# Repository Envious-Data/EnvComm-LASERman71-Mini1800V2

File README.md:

# EnvComm-LASERman71-Mini1800V2
 A custom keyboard commissioned by Laserman71

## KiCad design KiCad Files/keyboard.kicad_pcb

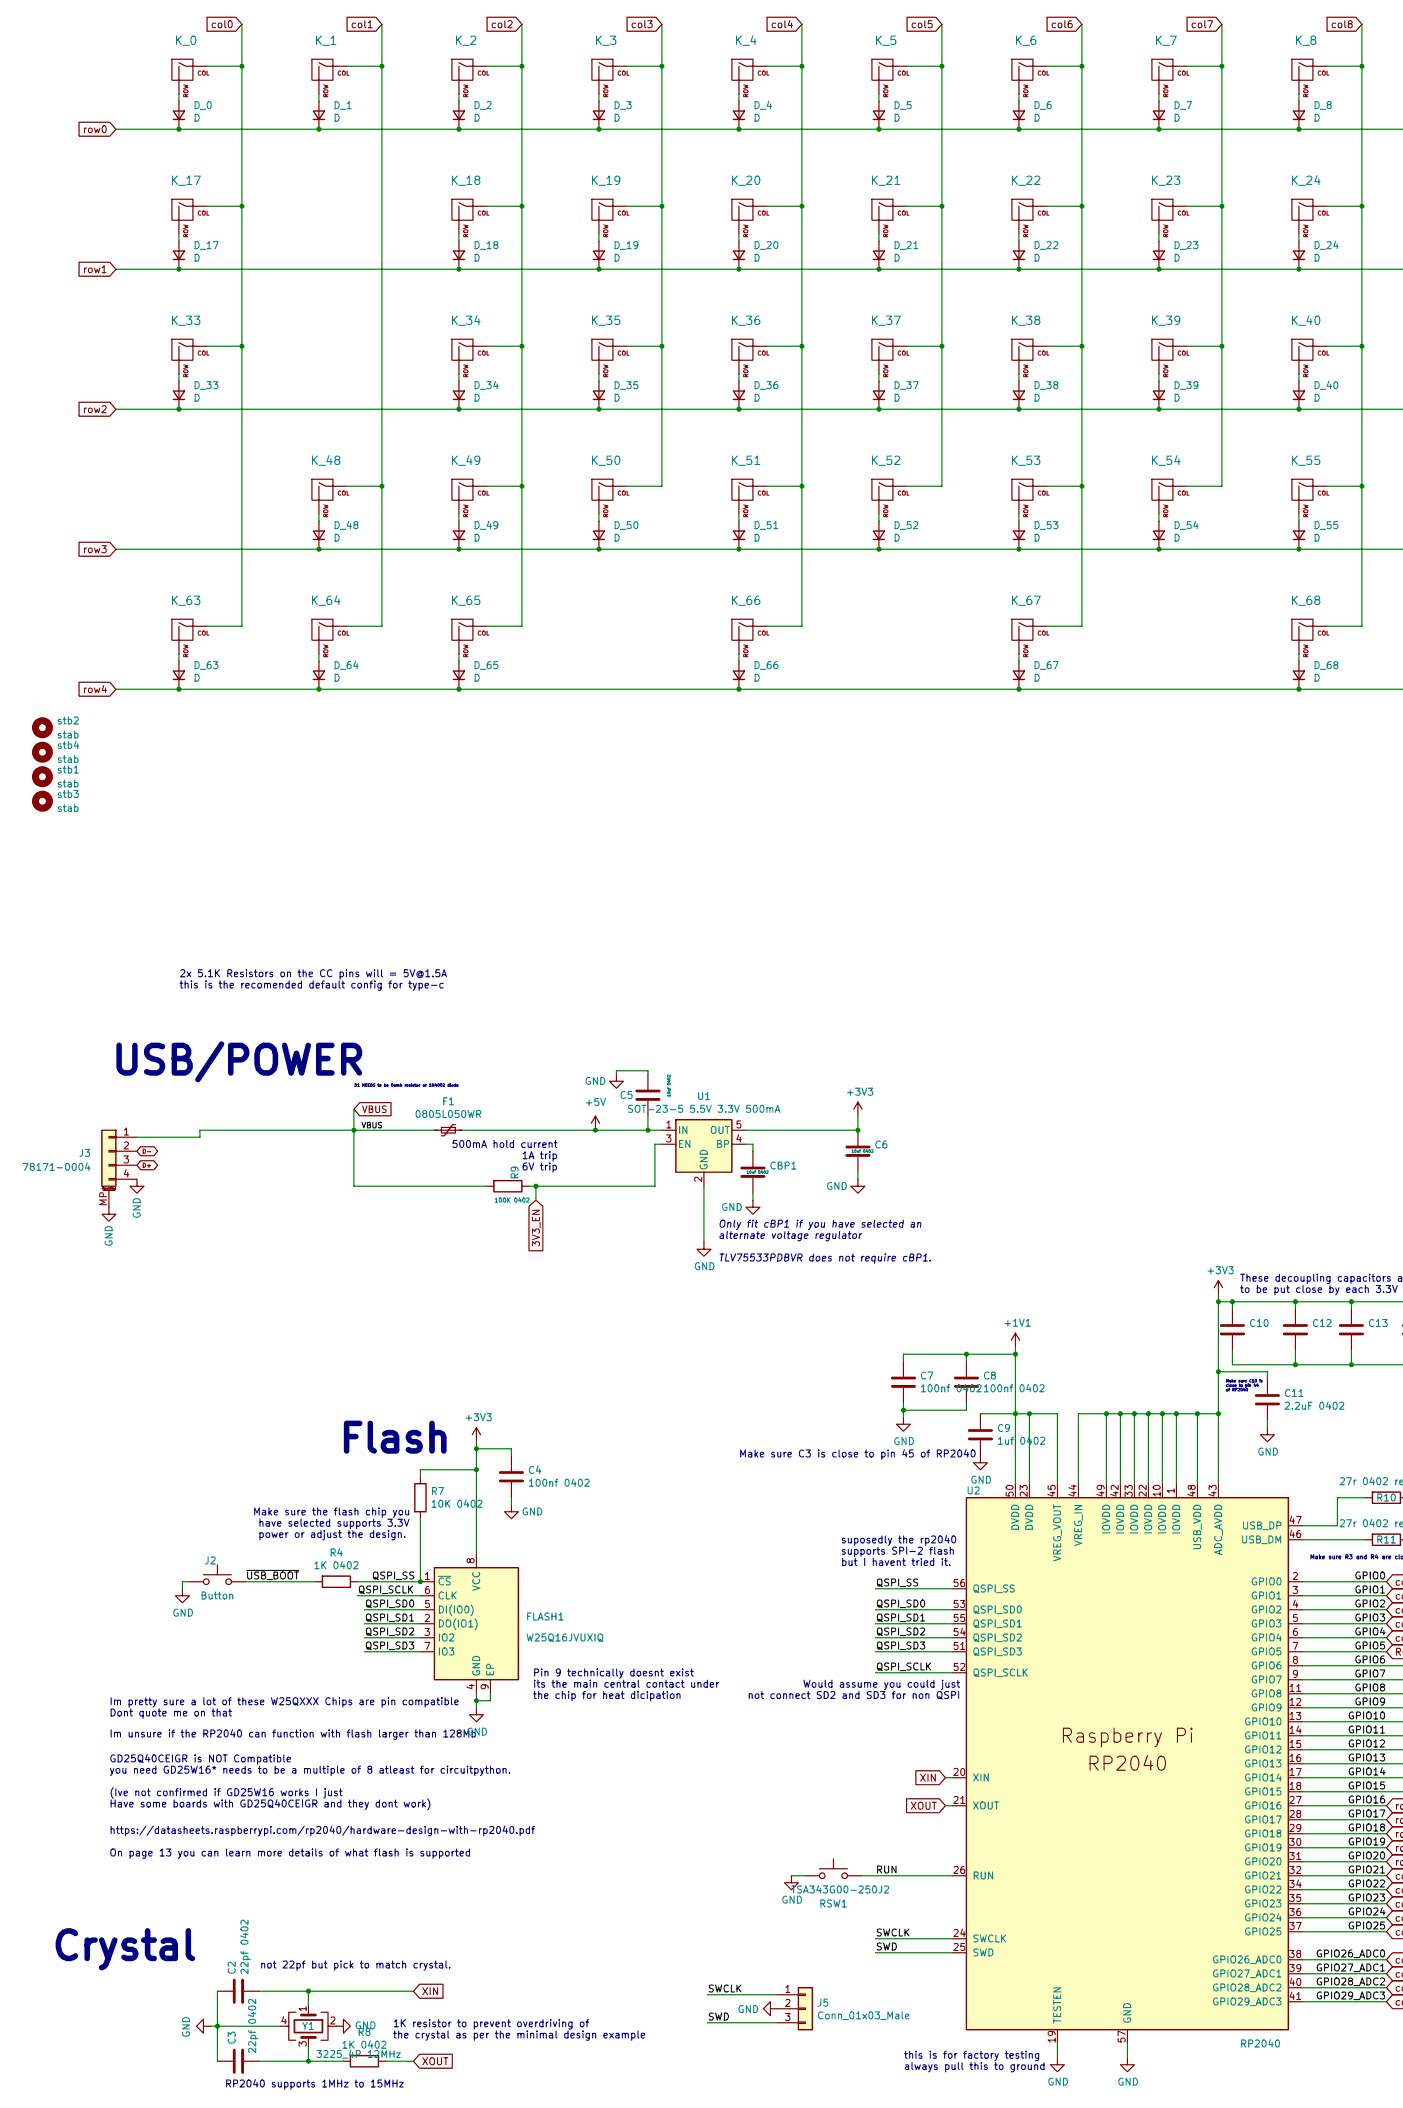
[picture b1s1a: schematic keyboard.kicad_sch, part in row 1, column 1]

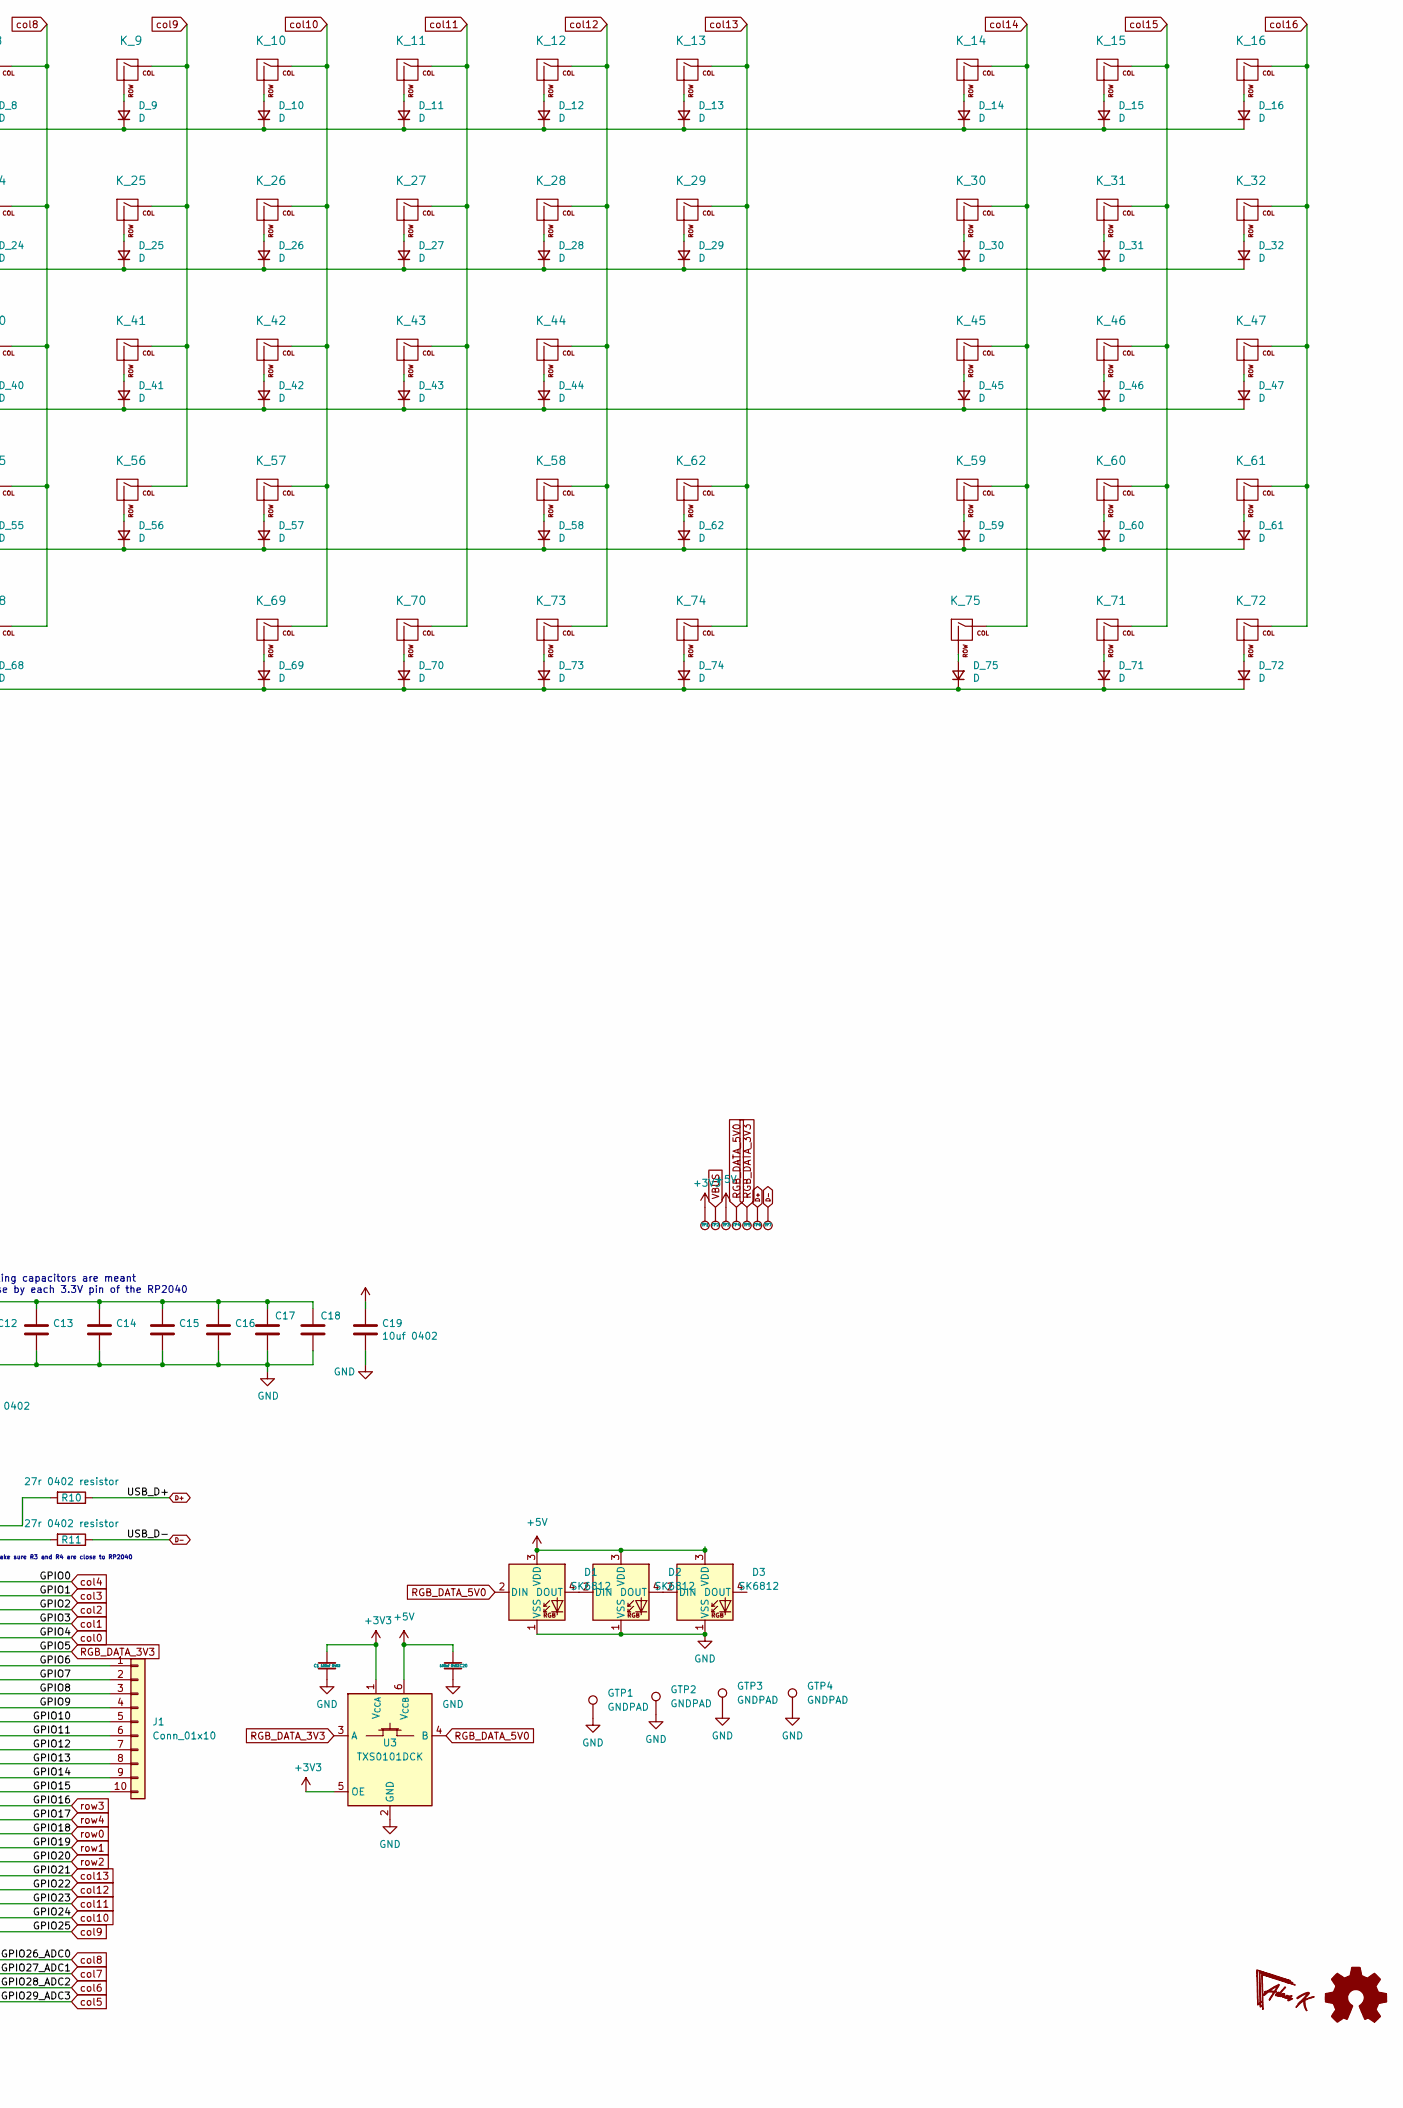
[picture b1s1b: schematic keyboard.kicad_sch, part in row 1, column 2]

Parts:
C1, C4, C7, C8, C10, C12, C13, C14, C15, C16, C17, C18, C20: 100nf 0402; C_0402_1005Metric
C2, C3: 22pf 0402; C_0402_1005Metric
C5, C6, C19: 10uf 0402; C_0402_1005Metric
C9: 1uf 0402; C_0402_1005Metric
C11: 2.2uF 0402; C_0402_1005Metric
CBP1: 10uf 0402; C_0402_1005Metric
D1, D2, D3: SK6812; SK6812-MINI-E
D_0, D_1, D_2, D_3, D_4, D_5, D_6, D_7, D_8, D_9, D_10, D_11, D_12, D_13, D_14, D_15, D_16, D_17, D_18, D_19, D_20, D_21, D_22, D_23, D_24, D_25, D_26, D_27, D_28, D_29, D_30, D_31, D_32, D_33, D_34, D_35, D_36, D_37, D_38, D_39, D_40, D_41, D_42, D_43, D_44, D_45, D_46, D_47, D_48, D_49, D_50, D_51, D_52, D_53, D_54, D_55, D_56, D_57, D_58, D_59, D_60, D_61, D_62, D_63, D_64, D_65, D_66, D_67, D_68, D_69, D_70, D_71, D_72, D_73, D_74, D_75: D; D_SOD-123
F1: 0805L050WR; Fuse_0805_2012Metric
FLASH1: W25Q16JVUXIQ; SON-8-1EP_3x2mm_P0.5mm_EP1.4x1.6mm
GTP1, GTP2, GTP3, GTP4: GNDPAD; SolderWire-0.1sqmm_1x01_D0.4mm_OD1mm
J1: Conn_01x10; PinHeader_1x10_P1.00mm_Vertical
J2: Button; SW_Push_SPST_NO_Alps_SKRK
J3: 78171-0004; MOLEX_781710004; Manufacturer Part Number 78171-0004; LCSC Part Number C588524
J5: Conn_01x03_Male; PinHeader_1x03_P2.54mm_Vertical
K_0, K_1, K_2, K_3, K_4, K_5, K_6, K_7, K_8, K_9, K_10, K_11, K_12, K_13, K_14, K_15, K_16, K_17, K_18, K_19, K_20, K_21, K_22, K_23, K_24, K_25, K_26, K_27, K_28, K_29, K_30, K_31, K_32, K_33, K_34, K_35, K_36, K_37, K_38, K_39, K_40, K_41, K_42, K_43, K_44, K_45, K_46, K_47, K_48, K_49, K_50, K_51, K_52, K_53, K_54, K_55, K_56, K_57, K_58, K_59, K_60, K_61, K_62, K_63, K_64, K_65, K_66, K_67, K_68, K_69, K_70, K_71, K_72, K_73, K_74, K_75: KEYSW; MXOnly-1U-NoLED
R4, R8: 1K 0402; R_0402_1005Metric
R7: 10K 0402; R_0402_1005Metric
R9: 100K 0402; R_0402_1005Metric
R10, R11: 27r 0402 resistor; R_0402_1005Metric
RSW1: TSA343G00-250J2; SW_Push_SPST_NO_Alps_SKRK
TP1, TP2, TP3, TP4, TP5, TP6, TP7: TestPoint; TestPoint_Pad_D1.0mm
U1: SOT-23-5 5.5V 3.3V 500mA; SOT-23-5
U2: RP2040; RP2040-QFN-56; LCSC C2040
U3: TXS0101DCK; SOT-363_SC-70-6
Y1: 3225_4P 12MHz; Crystal_SMD_3225-4Pin_3.2x2.5mm
stb1, stb2, stb3, stb4: stab; Stabilizer_Cherry_MX_2u

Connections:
3V3_EN: R9.1, U1.3 (EN)
+1V1: C7.1, C8.1, C9.1, U2.23 (DVDD), U2.45 (VREG_VOUT), U2.50 (DVDD)
+3V3: C1.1, C4.1, C6.1, C10.1, C11.1, C12.1, C13.1, C14.1, C15.1, C16.1, C17.1, C18.1, C19.1, FLASH1.8 (VCC), R7.1, TP1.1, U1.5 (OUT), U2.1 (IOVDD), U2.10 (IOVDD), U2.22 (IOVDD), U2.33 (IOVDD), U2.42 (IOVDD), U2.43 (ADC_AVDD), U2.44 (VREG_IN), U2.48 (USB_VDD), U2.49 (IOVDD), U3.1 (V_{CCA}), U3.5 (OE)
+5V: C5.1, C20.1, D1.3 (VDD), D2.3 (VDD), D3.3 (VDD), F1.1, TP3.1, U1.1 (IN), U3.6 (V_{CCB})
/GPIO6: J1.1, U2.8 (GPIO6)
/GPIO7: J1.2, U2.9 (GPIO7)
/GPIO8: J1.3, U2.11 (GPIO8)
/GPIO9: J1.4, U2.12 (GPIO9)
/GPIO10: J1.5, U2.13 (GPIO10)
/GPIO11: J1.6, U2.14 (GPIO11)
/GPIO12: J1.7, U2.15 (GPIO12)
/GPIO13: J1.8, U2.16 (GPIO13)
/GPIO14: J1.9, U2.17 (GPIO14)
/GPIO15: J1.10, U2.18 (GPIO15)
/QSPI_SCLK: FLASH1.6 (CLK), U2.52 (QSPI_SCLK)
/QSPI_SD0: FLASH1.5 (DI(IO0)), U2.53 (QSPI_SD0)
/QSPI_SD1: FLASH1.2 (DO(IO1)), U2.55 (QSPI_SD1)
/QSPI_SD2: FLASH1.3 (IO2), U2.54 (QSPI_SD2)
/QSPI_SD3: FLASH1.7 (IO3), U2.51 (QSPI_SD3)
/QSPI_SS: FLASH1.1 (~CS), R4.1, R7.2, U2.56 (QSPI_SS)
/RUN: RSW1.2, U2.26 (RUN)
/SWCLK: J5.1, U2.24 (SWCLK)
/SWD: J5.3, U2.25 (SWD)
/~USB_BOOT: J2.1, R4.2
D+: J3.3, R10.1, TP6.1
D-: J3.2, R11.1, TP7.1
GND: C1.2, C2.1, C3.1, C4.2, C5.2, C6.2, C7.2, C8.2, C9.2, C10.2, C11.2, C12.2, C13.2, C14.2, C15.2, C16.2, C17.2, C18.2, C19.2, C20.2, CBP1.2, D1.1 (VSS), D2.1 (VSS), D3.1 (VSS), FLASH1.4 (GND), FLASH1.9 (EP), GTP1.1, GTP2.1, GTP3.1, GTP4.1, J2.2, J3.4, J3.MP (MountPin), J5.2, RSW1.1, U1.2 (GND), U2.19 (TESTEN), U2.57 (GND), U3.2 (GND), Y1.2, Y1.4
unnamed: C3.2, R8.2, Y1.3
unnamed: D1.4 (DOUT), D2.2 (DIN)
unnamed: D2.4 (DOUT), D3.2 (DIN)
unnamed: D_0.2 (A), K_0.2 (ROW)
unnamed: D_1.2 (A), K_1.2 (ROW)
unnamed: D_2.2 (A), K_2.2 (ROW)
unnamed: D_3.2 (A), K_3.2 (ROW)
unnamed: D_4.2 (A), K_4.2 (ROW)
unnamed: D_5.2 (A), K_5.2 (ROW)
unnamed: D_6.2 (A), K_6.2 (ROW)
unnamed: D_7.2 (A), K_7.2 (ROW)
unnamed: D_8.2 (A), K_8.2 (ROW)
unnamed: D_9.2 (A), K_9.2 (ROW)
unnamed: D_10.2 (A), K_10.2 (ROW)
unnamed: D_11.2 (A), K_11.2 (ROW)
unnamed: D_12.2 (A), K_12.2 (ROW)
unnamed: D_13.2 (A), K_13.2 (ROW)
unnamed: D_14.2 (A), K_14.2 (ROW)
unnamed: D_15.2 (A), K_15.2 (ROW)
unnamed: D_16.2 (A), K_16.2 (ROW)
unnamed: D_17.2 (A), K_17.2 (ROW)
unnamed: D_18.2 (A), K_18.2 (ROW)
unnamed: D_19.2 (A), K_19.2 (ROW)
unnamed: D_20.2 (A), K_20.2 (ROW)
unnamed: D_21.2 (A), K_21.2 (ROW)
unnamed: D_22.2 (A), K_22.2 (ROW)
unnamed: D_23.2 (A), K_23.2 (ROW)
unnamed: D_24.2 (A), K_24.2 (ROW)
unnamed: D_25.2 (A), K_25.2 (ROW)
unnamed: D_26.2 (A), K_26.2 (ROW)
unnamed: D_27.2 (A), K_27.2 (ROW)
unnamed: D_28.2 (A), K_28.2 (ROW)
unnamed: D_29.2 (A), K_29.2 (ROW)
unnamed: D_30.2 (A), K_30.2 (ROW)
unnamed: D_31.2 (A), K_31.2 (ROW)
unnamed: D_32.2 (A), K_32.2 (ROW)
unnamed: D_33.2 (A), K_33.2 (ROW)
unnamed: D_34.2 (A), K_34.2 (ROW)
unnamed: D_35.2 (A), K_35.2 (ROW)
unnamed: D_36.2 (A), K_36.2 (ROW)
unnamed: D_37.2 (A), K_37.2 (ROW)
unnamed: D_38.2 (A), K_38.2 (ROW)
unnamed: D_39.2 (A), K_39.2 (ROW)
unnamed: D_40.2 (A), K_40.2 (ROW)
unnamed: D_41.2 (A), K_41.2 (ROW)
unnamed: D_42.2 (A), K_42.2 (ROW)
unnamed: D_43.2 (A), K_43.2 (ROW)
unnamed: D_44.2 (A), K_44.2 (ROW)
unnamed: D_45.2 (A), K_45.2 (ROW)
unnamed: D_46.2 (A), K_46.2 (ROW)
unnamed: D_47.2 (A), K_47.2 (ROW)
unnamed: D_48.2 (A), K_48.2 (ROW)
unnamed: D_49.2 (A), K_49.2 (ROW)
unnamed: D_50.2 (A), K_50.2 (ROW)
unnamed: D_51.2 (A), K_51.2 (ROW)
unnamed: D_52.2 (A), K_52.2 (ROW)
unnamed: D_53.2 (A), K_53.2 (ROW)
unnamed: D_54.2 (A), K_54.2 (ROW)
unnamed: D_55.2 (A), K_55.2 (ROW)
unnamed: D_56.2 (A), K_56.2 (ROW)
unnamed: D_57.2 (A), K_57.2 (ROW)
unnamed: D_58.2 (A), K_58.2 (ROW)
unnamed: D_59.2 (A), K_59.2 (ROW)
unnamed: D_60.2 (A), K_60.2 (ROW)
unnamed: D_61.2 (A), K_61.2 (ROW)
unnamed: D_62.2 (A), K_62.2 (ROW)
unnamed: D_63.2 (A), K_63.2 (ROW)
unnamed: D_64.2 (A), K_64.2 (ROW)
unnamed: D_65.2 (A), K_65.2 (ROW)
unnamed: D_66.2 (A), K_66.2 (ROW)
unnamed: D_67.2 (A), K_67.2 (ROW)
unnamed: D_68.2 (A), K_68.2 (ROW)
unnamed: D_69.2 (A), K_69.2 (ROW)
unnamed: D_70.2 (A), K_70.2 (ROW)
unnamed: D_71.2 (A), K_71.2 (ROW)
unnamed: D_72.2 (A), K_72.2 (ROW)
unnamed: D_73.2 (A), K_73.2 (ROW)
unnamed: D_74.2 (A), K_74.2 (ROW)
unnamed: D_75.2 (A), K_75.2 (ROW)
unnamed: CBP1.1, U1.4 (BP)
unnamed: R11.2, U2.46 (USB_DM)
unnamed: R10.2, U2.47 (USB_DP)
RGB_DATA_3V3: TP5.1, U2.7 (GPIO5), U3.3 (A)
RGB_DATA_5V0: D1.2 (DIN), TP4.1, U3.4 (B)
VBUS: F1.2, J3.1, R9.2, TP2.1
XIN: C2.2, U2.20 (XIN), Y1.1
XOUT: R8.1, U2.21 (XOUT)
col0: K_0.1 (COL), K_17.1 (COL), K_33.1 (COL), K_63.1 (COL), U2.6 (GPIO4)
col1: K_1.1 (COL), K_48.1 (COL), K_64.1 (COL), U2.5 (GPIO3)
col2: K_2.1 (COL), K_18.1 (COL), K_34.1 (COL), K_49.1 (COL), K_65.1 (COL), U2.4 (GPIO2)
col3: K_3.1 (COL), K_19.1 (COL), K_35.1 (COL), K_50.1 (COL), U2.3 (GPIO1)
col4: K_4.1 (COL), K_20.1 (COL), K_36.1 (COL), K_51.1 (COL), K_66.1 (COL), U2.2 (GPIO0)
col5: K_5.1 (COL), K_21.1 (COL), K_37.1 (COL), K_52.1 (COL), U2.41 (GPIO29_ADC3)
col6: K_6.1 (COL), K_22.1 (COL), K_38.1 (COL), K_53.1 (COL), K_67.1 (COL), U2.40 (GPIO28_ADC2)
col7: K_7.1 (COL), K_23.1 (COL), K_39.1 (COL), K_54.1 (COL), U2.39 (GPIO27_ADC1)
col8: K_8.1 (COL), K_24.1 (COL), K_40.1 (COL), K_55.1 (COL), K_68.1 (COL), U2.38 (GPIO26_ADC0)
col9: K_9.1 (COL), K_25.1 (COL), K_41.1 (COL), K_56.1 (COL), U2.37 (GPIO25)
col10: K_10.1 (COL), K_26.1 (COL), K_42.1 (COL), K_57.1 (COL), K_69.1 (COL), U2.36 (GPIO24)
col11: K_11.1 (COL), K_27.1 (COL), K_43.1 (COL), K_70.1 (COL), U2.35 (GPIO23)
col12: K_12.1 (COL), K_28.1 (COL), K_44.1 (COL), K_58.1 (COL), K_73.1 (COL), U2.34 (GPIO22)
col13: K_13.1 (COL), K_29.1 (COL), K_62.1 (COL), K_74.1 (COL), U2.32 (GPIO21)
col14: K_14.1 (COL), K_30.1 (COL), K_45.1 (COL), K_59.1 (COL), K_75.1 (COL)
col15: K_15.1 (COL), K_31.1 (COL), K_46.1 (COL), K_60.1 (COL), K_71.1 (COL)
col16: K_16.1 (COL), K_32.1 (COL), K_47.1 (COL), K_61.1 (COL), K_72.1 (COL)
row0: D_0.1 (K), D_1.1 (K), D_2.1 (K), D_3.1 (K), D_4.1 (K), D_5.1 (K), D_6.1 (K), D_7.1 (K), D_8.1 (K), D_9.1 (K), D_10.1 (K), D_11.1 (K), D_12.1 (K), D_13.1 (K), D_14.1 (K), D_15.1 (K), D_16.1 (K), U2.29 (GPIO18)
row1: D_17.1 (K), D_18.1 (K), D_19.1 (K), D_20.1 (K), D_21.1 (K), D_22.1 (K), D_23.1 (K), D_24.1 (K), D_25.1 (K), D_26.1 (K), D_27.1 (K), D_28.1 (K), D_29.1 (K), D_30.1 (K), D_31.1 (K), D_32.1 (K), U2.30 (GPIO19)
row2: D_33.1 (K), D_34.1 (K), D_35.1 (K), D_36.1 (K), D_37.1 (K), D_38.1 (K), D_39.1 (K), D_40.1 (K), D_41.1 (K), D_42.1 (K), D_43.1 (K), D_44.1 (K), D_45.1 (K), D_46.1 (K), D_47.1 (K), U2.31 (GPIO20)
row3: D_48.1 (K), D_49.1 (K), D_50.1 (K), D_51.1 (K), D_52.1 (K), D_53.1 (K), D_54.1 (K), D_55.1 (K), D_56.1 (K), D_57.1 (K), D_58.1 (K), D_59.1 (K), D_60.1 (K), D_61.1 (K), D_62.1 (K), U2.27 (GPIO16)
row4: D_63.1 (K), D_64.1 (K), D_65.1 (K), D_66.1 (K), D_67.1 (K), D_68.1 (K), D_69.1 (K), D_70.1 (K), D_71.1 (K), D_72.1 (K), D_73.1 (K), D_74.1 (K), D_75.1 (K), U2.28 (GPIO17)

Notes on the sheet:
Make sure C10 is close to pin 44 of RP2040
GD25Q40CEIGR is NOT Compatible you need GD25W16* needs to be a multiple of 8 atleast for circuitpython. (Ive not confirmed if GD25W16 works I just Have some boards with GD25Q40CEIGR and they dont work)
Im unsure if the RP2040 can function with flash larger than 128Mb
Crystal
suposedly the rp2040 supports SPI-2 flash but I havent tried it.
https://datasheets.raspberrypi.com/rp2040/hardware-design-with-rp2040.pdf On page 13 you can learn more details of what flash is supported
Im pretty sure a lot of these W25QXXX Chips are pin compatible Dont quote me on that
USB/POWER
Only fit cBP1 if you have selected an alternate voltage regulator TLV75533PDBVR does not require cBP1.
RP2040 supports 1MHz to 15MHz
this is for factory testing always pull this to ground
Make sure R3 and R4 are close to RP2040
These decoupling capacitors are meant to be put close by each 3.3V pin of the RP2040
1K resistor to prevent overdriving of the crystal as per the minimal design example
500mA hold current 1A trip 6V trip
Make sure C3 is close to pin 45 of RP2040
D1 NEEDS to be 0omh resistor or 1N4002 diode
Flash
2x 5.1K Resistors on the CC pins will = 5V@1.5A this is the recomended default config for type-c
not 22pf but pick to match crystal.
Would assume you could just not connect SD2 and SD3 for non QSPI
Pin 9 technically doesnt exist its the main central contact under the chip for heat dicipation
Make sure the flash chip you have selected supports 3.3V power or adjust the design.

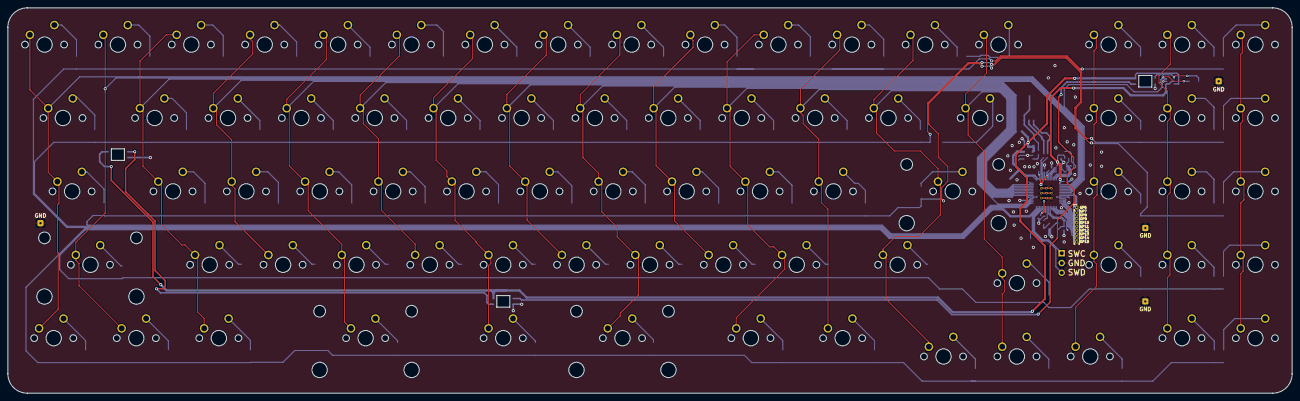
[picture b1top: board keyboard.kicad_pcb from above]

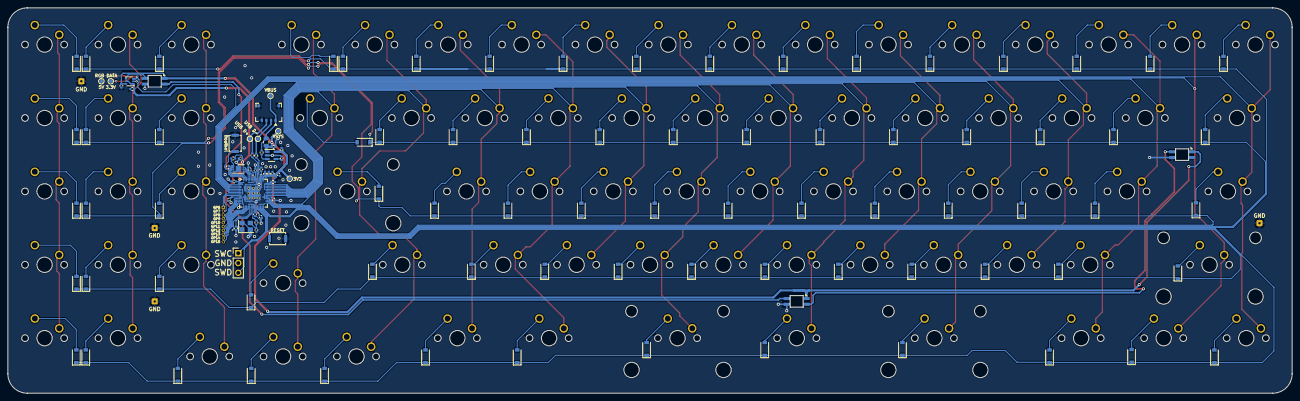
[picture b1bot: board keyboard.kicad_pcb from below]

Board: 2 copper layers, 333.4 x 100.0 mm, 208 parts (123 on the bottom side), 136 nets.

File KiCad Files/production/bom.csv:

Designator,Footprint,Quantity,Value,LCSC Part #
"C1, C10, C12, C13, C14, C15, C16, C17, C18, C20, C4, C7, C8",0402,13,100nf 0402, 
C11,0402,1,2.2uF 0402, 
"C19, C5, C6, CBP1",0402,4,10uf 0402, 
"C2, C3",0402,2,22pf 0402, 
C9,0402,1,1uf 0402, 
"D1, D2, D3",SK6812-MINI-E,3,SK6812,
"D_0, D_1, D_10, D_11, D_12, D_13, D_14, D_15, D_16, D_17, D_18, D_19, D_2, D_20, D_21, D_22, D_23, D_24, D_25, D_26, D_27, D_28, D_29, D_3, D_30, D_31, D_32, D_33, D_34, D_35, D_36, D_37, D_38, D_39, D_4, D_40, D_41, D_42, D_43, D_44, D_45, D_46, D_47, D_48, D_49, D_5, D_50, D_51, D_52, D_53, D_54, D_55, D_56, D_57, D_58, D_59, D_6, D_60, D_61, D_62, D_63, D_64, D_65, D_66, D_67, D_68, D_69, D_7, D_70, D_71, D_72, D_73, D_74, D_75, D_8, D_9",D_SOD-123,76,D,
F1,0805,1,0805L050WR,
FLASH1,SON-8-1EP_3x2mm_P0.5mm_EP1.4x1.6mm,1,W25Q16JVUXIQ,
"GTP1, GTP2, GTP3, GTP4",SolderWire-0.1sqmm_1x01_D0.4mm_OD1mm,4,GNDPAD,
J1,PinHeader_1x10_P1.00mm_Vertical,1,Conn_01x10,
J2,SW_Push_SPST_NO_Alps_SKRK,1,Button, 
J3,MOLEX_781710004,1,78171-0004,
J5,PinHeader_1x03_P2.54mm_Vertical,1,Conn_01x03_Male, 
"K_0, K_1, K_10, K_11, K_12, K_13, K_14, K_15, K_16, K_17, K_18, K_19, K_2, K_20, K_21, K_22, K_23, K_24, K_25, K_26, K_27, K_28, K_29, K_3, K_30, K_31, K_32, K_33, K_34, K_35, K_36, K_37, K_38, K_39, K_4, K_40, K_41, K_42, K_43, K_44, K_45, K_46, K_47, K_48, K_49, K_5, K_50, K_51, K_52, K_53, K_54, K_55, K_56, K_57, K_58, K_59, K_6, K_60, K_61, K_62, K_63, K_64, K_65, K_66, K_67, K_68, K_69, K_7, K_70, K_71, K_72, K_73, K_74, K_75, K_8, K_9",MXOnly-1U-NoLED,76,KEYSW,
"R10, R11",0402,2,27r 0402 resistor, 
"R4, R8",0402,2,1K 0402, 
R7,0402,1,10K 0402,  
R9,0402,1,100K 0402, 
RSW1,SW_Push_SPST_NO_Alps_SKRK,1,TSA343G00-250J2,
"TP1, TP2, TP3, TP4, TP5, TP6, TP7",TestPoint_Pad_D1.0mm,7,TestPoint,
U1,SOT-23-5,1,SOT-23-5 5.5V 3.3V 500mA, 
U2,RP2040-QFN-56,1,RP2040, C2040
U3,SOT-363_SC-70-6,1,TXS0101DCK,
Y1,Crystal_SMD_3225-4Pin_3.2x2.5mm,1,3225_4P 12MHz, 
"stb1, stb2, stb3, stb4",Stabilizer_Cherry_MX_2u,4,stab,

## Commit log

2024-03-14 Initial Commit +1
2024-03-14 routed matrix and updated git ignore
2024-03-17 added silkscreen markings, broke out unused GPIOs, cleaned up board, ran DRC and cleaned up traces.
2024-03-19 exported 3d model to design case
2024-03-22 added test points, cleaned up PCB, Generated production files
2024-03-24 rotated udb-s connector as requested and generated updated production files
2024-04-06 corrected two major issues, columns 14,15 and 16 were not connected to any GPIOs, the LED footprints were incorrect for reverse mount.
2024-04-06 added KLE data for later use
2024-05-07 added stabilizer 3d models to verify dimensions
2024-11-04 moved buttons, re-routed traces and updated footprints.
